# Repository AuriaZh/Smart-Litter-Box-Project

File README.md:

# TECHIN-514 Smart Litter Box Project

# Background
My cat was recently diagnosed with diabetes, so I have to closely monitor her weight and urination frequency. According to my vet, diabetic cats should typically urinate between 2-4 times per day, and anything more than that could indicate poor blood sugar control or other health issues. Other than that, weight management is also essential, so I have to keep daily records of her to prevent unexpected changes in advance. However, cats tend to have an unpredictable litter box routine, which became a big challenge for students like me who must go to school every day. 

# Proposed Solution
This is a smart litter box designed for cats with diabetes. It aims to help owners closely monitor their cats' weight changes and urination frequency. With Bluetooth transmission support, owners can access real-time data anytime through cloud database.

# Desired Features
HX711 and 4 Load Cells to measure weight changes and detect urination frequency.
2 Xiao Esp32C3 to transmit data wirelessly via Bluetooth
A stepper motor-driven gauge displays daily urination frequency once it receives data.
Runs on a battery-efficient system optimized for long-term operation.

# System Communication Diagram
This System Communication Diagram shows how the load cells detect weight, the HX711 amplifies the signal, and the Sensor ESP32 processes and sends data via Bluetooth to the Display ESP32, which controls the gauge display and LED indicator for real-time feedback.

# Detailed Diagram
This System Diagram represents the Smart Litter Box for Diabetic Cats. The load cells measure weight, and the HX711 module amplifies and converts the signal. The Sensor ESP32 processes the data and transmits it via Bluetooth to the Display ESP32, which controls the stepper motor gauge display to show visits and the LED as a status indicator.

# Critical Components & PCB
Schematic diagram

PCB Design

Soldered PCB

# 3D modeling
Fusion Link: https://a360.co/4hFX8mK

3D model enclosure for sensor device

3D model enclosure for display device

# Litter box 3D Render

# Prototyping
3D printed devices

# Final Product

# Working Video
Youtube Link: https://youtu.be/_8Va8JSGBe8

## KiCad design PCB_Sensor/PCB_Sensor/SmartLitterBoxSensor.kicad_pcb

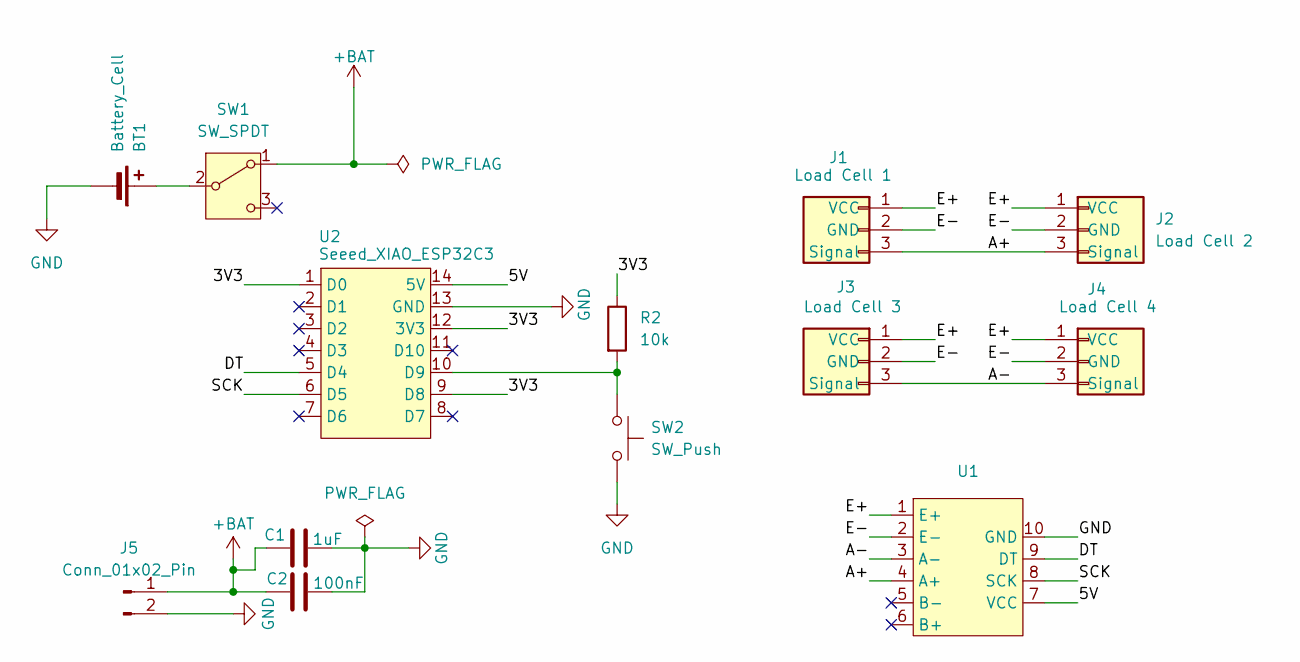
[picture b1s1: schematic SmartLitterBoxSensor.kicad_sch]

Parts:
BT1: Battery_Cell; JST_PH_B2B-PH-K_1x02_P2.00mm_Vertical
C1: 1uF; C_1206_3216Metric
C2: 100nF; C_1206_3216Metric
J1: Load Cell 1; PinHeader_1x03_P2.54mm_Vertical
J2: Load Cell 2; PinHeader_1x03_P2.54mm_Vertical
J3: Load Cell 3; PinHeader_1x03_P2.54mm_Vertical
J4: Load Cell 4; PinHeader_1x03_P2.54mm_Vertical
J5: Conn_01x02_Pin; PinHeader_1x02_P2.54mm_Vertical
R2: 10k; R_1206_3216Metric
SW1: SW_SPDT; SW_SPDT_CK_JS102011SAQN
SW2: SW_Push; SW_PUSH_6mm
U1: HX711
U2: Seeed_XIAO_ESP32C3; Seeed XIAO ESP32C3

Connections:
+BAT: C1.1, C2.1, J5.1, SW1.1 (A)
/3V3: R2.1, U2.1 (D0), U2.9 (D8), U2.12 (3V3)
/5V: U1.7 (VCC), U2.14 (5V)
/A+: J1.3 (Signal), J2.3 (Signal), U1.4 (A+)
/A-: J3.3 (Signal), J4.3 (Signal), U1.3 (A-)
/DT: U1.9 (DT), U2.5 (D4)
/E+: J1.1 (VCC), J2.1 (VCC), J3.1 (VCC), J4.1 (VCC), U1.1 (E+)
/E-: J1.2 (GND), J2.2 (GND), J3.2 (GND), J4.2 (GND), U1.2 (E-)
/SCK: U1.8 (SCK), U2.6 (D5)
GND: BT1.2 (-), C1.2, C2.2, J5.2, SW2.2, U1.10 (GND), U2.13 (GND)
unnamed: BT1.1 (+), SW1.2 (B)
unnamed: R2.2, SW2.1, U2.10 (D9)

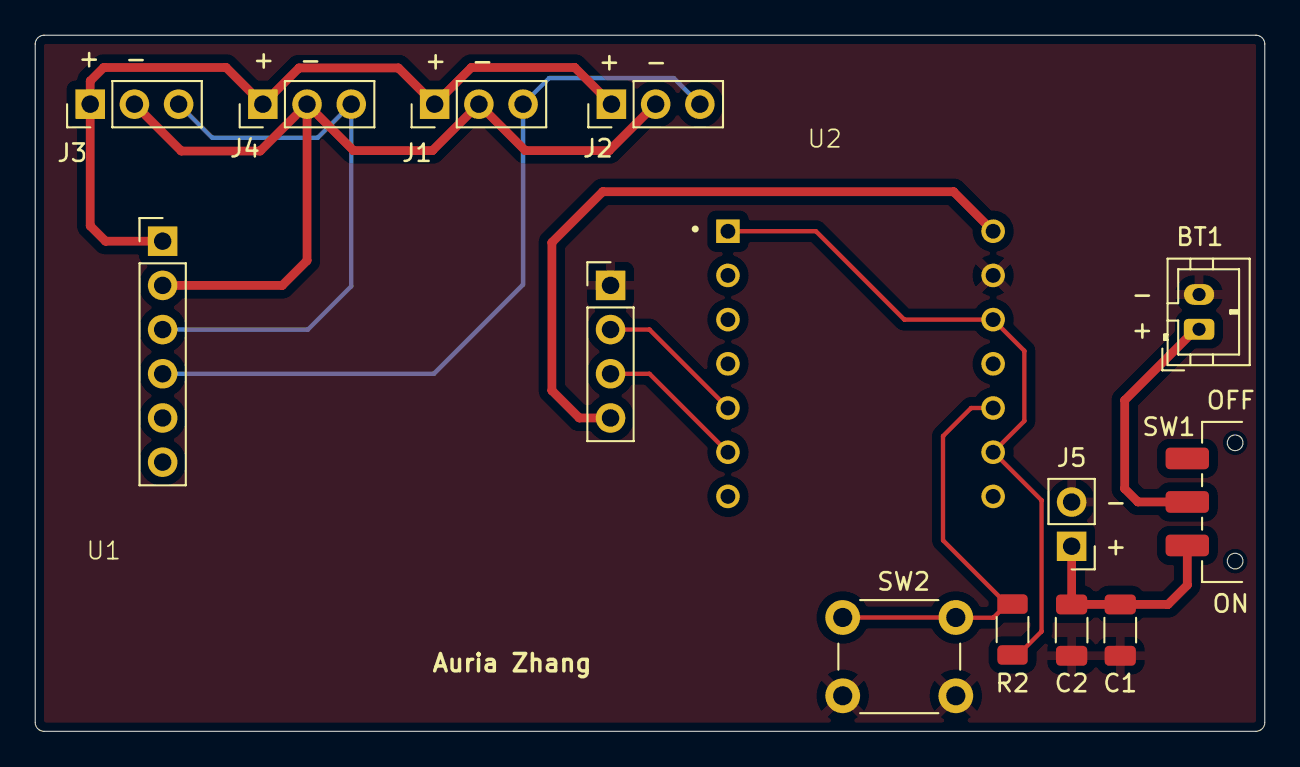
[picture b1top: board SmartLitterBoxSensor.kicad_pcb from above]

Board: 2 copper layers, 70.7 x 40.0 mm, 13 parts (0 on the bottom side), 12 nets.

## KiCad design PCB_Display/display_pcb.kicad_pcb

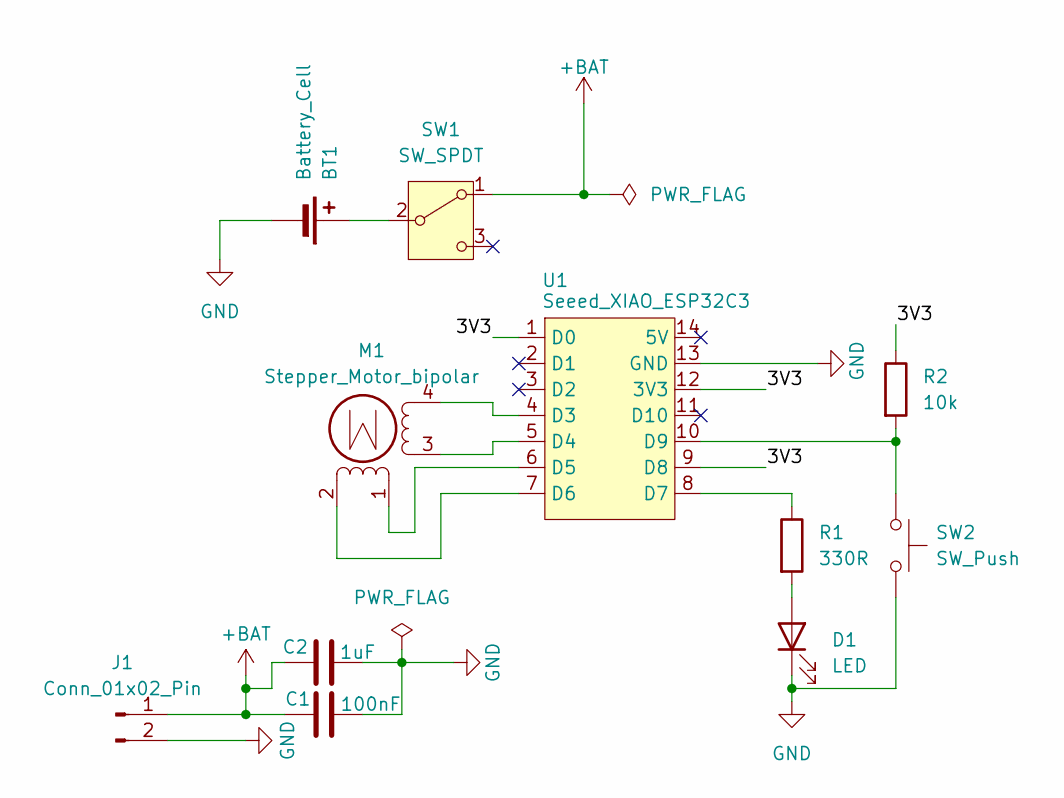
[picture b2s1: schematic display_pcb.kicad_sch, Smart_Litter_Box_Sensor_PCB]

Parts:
BT1: Battery_Cell; JST_PH_B2B-PH-K_1x02_P2.00mm_Vertical
C1: 100nF; C_1206_3216Metric
C2: 1uF; C_1206_3216Metric
D1: LED; LED_D5.0mm
J1: Conn_01x02_Pin; PinHeader_1x02_P2.54mm_Vertical
M1: Stepper_Motor_bipolar; X27-168
R1: 330R; R_1206_3216Metric
R2: 10k; R_1206_3216Metric
SW1: SW_SPDT; SW_SPDT_CK_JS102011SAQN
SW2: SW_Push; SW_PUSH_6mm
U1: Seeed_XIAO_ESP32C3; Seeed XIAO ESP32C3

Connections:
+BAT: C1.1, C2.1, J1.1, SW1.1 (A)
/3V3: R2.1, U1.1 (D0), U1.9 (D8), U1.12 (3V3)
GND: BT1.2 (-), C1.2, C2.2, D1.1 (K), J1.2, SW2.2, U1.13 (GND)
unnamed: BT1.1 (+), SW1.2 (B)
unnamed: D1.2 (A), R1.2
unnamed: M1.2 (-), U1.7 (D6)
unnamed: M1.4, U1.4 (D3)
unnamed: M1.3, U1.5 (D4)
unnamed: M1.1, U1.6 (D5)
unnamed: R1.1, U1.8 (D7)
unnamed: R2.2, SW2.1, U1.10 (D9)

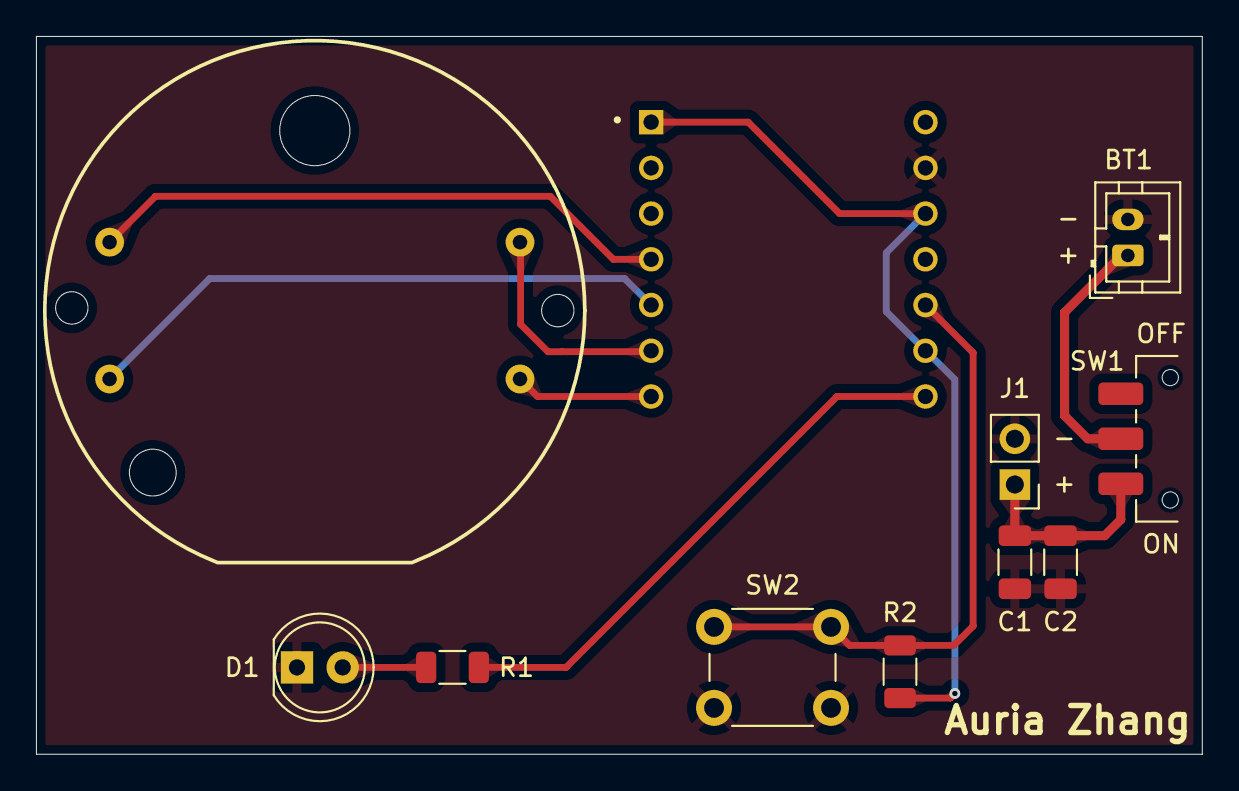
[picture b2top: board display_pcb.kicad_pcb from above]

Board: 2 copper layers, 64.8 x 39.9 mm, 11 parts (0 on the bottom side), 11 nets.

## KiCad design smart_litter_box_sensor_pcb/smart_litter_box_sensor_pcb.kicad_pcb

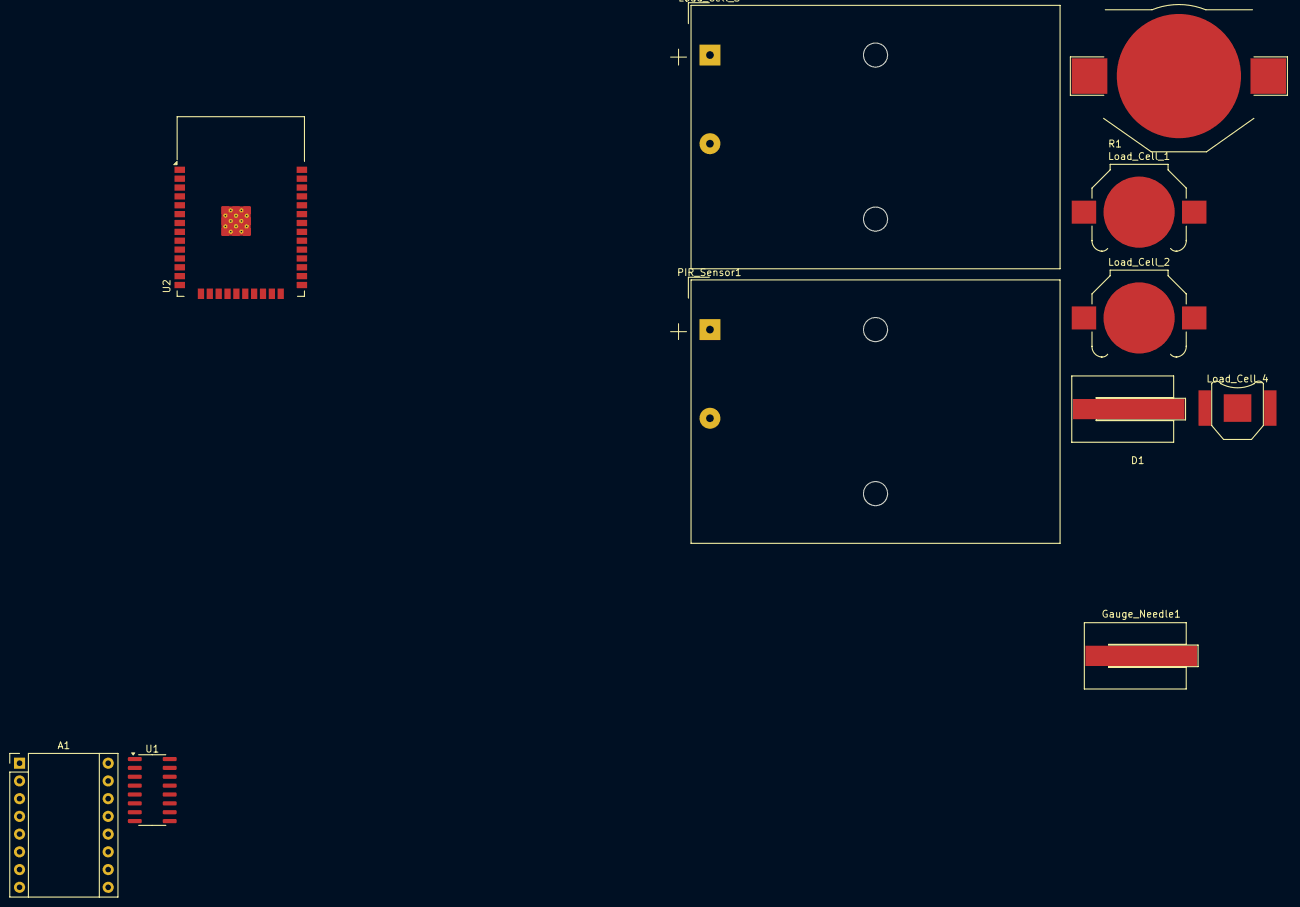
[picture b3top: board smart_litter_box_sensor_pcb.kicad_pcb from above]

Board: 2 copper layers, 11 parts (0 on the bottom side), 10 nets, no tracks yet.

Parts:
A1: A4988; Pololu_Breakout-16_15.2x20.3mm
D1: LED; BatteryHolder_Keystone_2993
Gauge_Needle1: Stepper_Motor_Gauge; BatteryHolder_Keystone_2993
Load_Cell_1, Load_Cell_2: Conn_01x04; BatteryHolder_Keystone_3000_1x12mm
Load_Cell_3: Conn_01x04; BatteryHolder_Keystone_2479_3xAAA
Load_Cell_4: Conn_01x04; BatteryHolder_Keystone_2998_1x6.8mm
PIR_Sensor1: HC-SR501; BatteryHolder_Keystone_2479_3xAAA
R1: R; BatteryHolder_Keystone_3002_1x2032
U1: HX711; SOP-16_3.9x9.9mm_P1.27mm
U2: ESP32-WROOM-32

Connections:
unnamed: A1.16 (DIR), U2.12 (IO27)
unnamed: A1.15 (STEP), U2.13 (IO14)
unnamed: A1.2 (VDD), PIR_Sensor1.1 (VCC), U2.2 (VDD)
unnamed: A1.9 (~ENABLE), D1.1 (K), U2.1 (GND), U2.15 (GND), U2.38 (GND), U2.39 (GND)
unnamed: Load_Cell_1.1 (Exc+), Load_Cell_2.1 (Exc+), Load_Cell_3.1 (Exc+), Load_Cell_4.1 (Exc+), U1.1 (VSUP)
unnamed: Load_Cell_1.2 (Exc-), Load_Cell_2.2 (Exc-), Load_Cell_3.2 (Exc-), Load_Cell_4.2 (Exc-), U1.5 (AGND)
unnamed: PIR_Sensor1.2 (OUT), U2.7 (IO35)
unnamed: U1.12 (DOUT), U2.26 (IO4)
unnamed: U1.11 (PD_SCK), U2.29 (IO5)
unnamed: R1.1, U2.6 (IO34)

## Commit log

2025-01-22 Updated images folder and removed old files
2025-01-22 Added .gitignore to exclude system files
2025-01-22 Updated README and added new sketch image
2025-01-22 Updated README with new image references
2025-02-14 Add files via upload
    Update the display part of the PCB
2025-02-14 Add files via upload
    Upload power analyzing for both sensor and display
2025-03-15 Add files via upload
    Upload code for both Load cells and Stepper Motor devices
2025-03-15 Add files via upload
    Upload updated 2 PCBs
2025-03-15 Add files via upload
    3D models for litter box and enclosure
